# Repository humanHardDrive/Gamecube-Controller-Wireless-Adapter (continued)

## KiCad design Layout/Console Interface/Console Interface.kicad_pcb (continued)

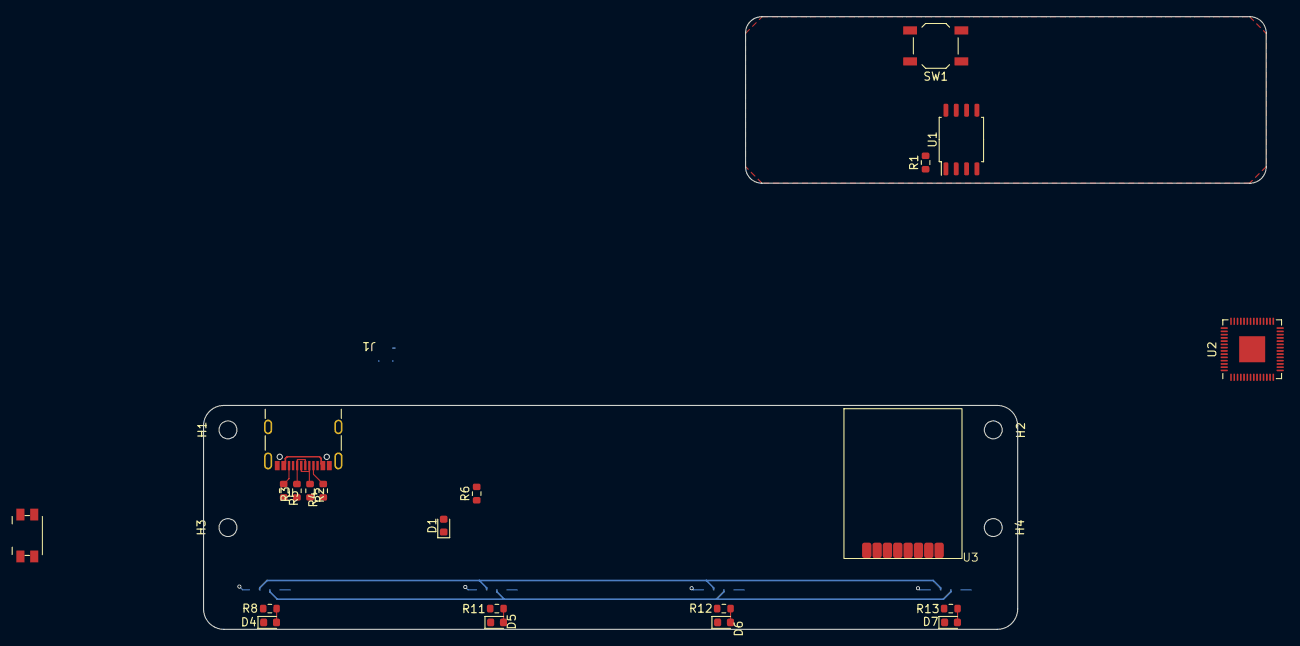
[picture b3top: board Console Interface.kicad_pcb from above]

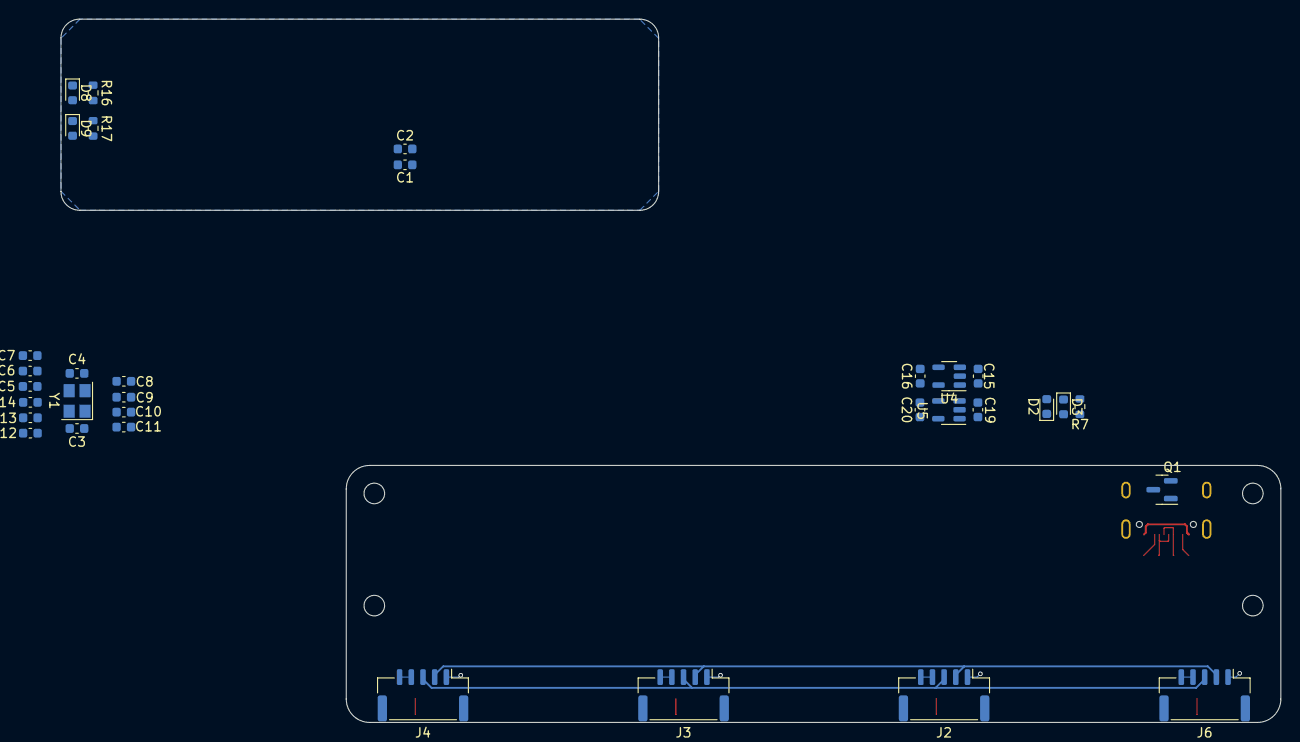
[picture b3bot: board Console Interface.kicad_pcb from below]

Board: 2 copper layers, 130.5 x 75.2 mm, 58 parts (33 on the bottom side), 46 nets.

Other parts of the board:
SW3: SW_PAIR; Panasonic_EVQPUK_EVQPUB

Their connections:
GND: SW3.2; also elsewhere on the board

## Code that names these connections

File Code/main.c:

#include <stdint.h>

#include "pico/stdlib.h"

#include "hardware/gpio.h"
#include "hardware/spi.h"

#include "PinDefs.h"
#include "Utils.h"

#include "ControllerComm.h"

int main()
{
    //Setup pins
    gpio_init(PAIR_PIN);
    gpio_init(FUNC_SEL_PIN);

    gpio_init(NRF_CS_PIN);
    gpio_init(NRF_CE_PIN);
    gpio_init(NRF_IRQ_PIN);

    gpio_set_dir(PAIR_PIN, GPIO_IN);
    gpio_set_dir(FUNC_SEL_PIN, GPIO_IN);

    gpio_pull_up(PAIR_PIN);
    gpio_pull_up(FUNC_SEL_PIN);

    //Setup SPI0
    spi_init(spi_default, 10000000); //NRF supports 10MHz
    gpio_set_function(SPI0_MOSI_PIN, GPIO_FUNC_SPI);
    gpio_set_function(SPI0_MISO_PIN, GPIO_FUNC_SPI);
    gpio_set_function(SPI0_CLK_PIN, GPIO_FUNC_SPI);

    //Detect device configuration
    if(!gpio_get(FUNC_SEL_PIN))
    {
        /*
        This is the controller side interface
        Poll for controller connection
        Poll for controller values
        Report controller values back to the console side interface
        */
       SetInterfaceType(CONTROLLER_SIDE_INTERFACE);
    }
    else
    {
        /*
        This is the console side interface
        Handle polling requests from the console
        Feed console data from controller side interface
        Communicate rumbe back to controller side interface
        */
       SetInterfaceType(CONSOLE_SIDE_INTERFACE);
    }

    ControllerComm_Init();

    while(1)
    {
        ControllerComm_Background();
    }

    return 0;
}

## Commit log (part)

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2024-03-02 Add parts to the controller interface
2024-03-02 Add code
2024-03-03 Add some code
2024-03-03 Fill out pin definitions. Start adding PIO
2024-03-03 Did stuff
2024-03-05 Fix errors
2024-03-05 Testing. Not working.
2024-03-07 Create new project to test controller interface
2024-03-15 Add rx.pio code. Testing
2024-03-15 Better transmit timing. Create loopback test.
    All data looks good. Out matches in for 16 bits
2024-03-15 Add comments
2024-03-15 Copy over working code
2024-03-16 Controller polling is done on a per controller timer
2024-03-17 Fix build
2024-03-17 Begin refactor tx/rx into single PIO
2024-03-17 Nevermind. No refactor
2024-03-17 Enable/disable driver to create open collector functionality. Add more communication interface logic
2024-03-19 Change test to use an open-drain configuration
2024-03-20 Controller adapter testing
2024-03-20 Fix bug setting data length back to a shorter range
2024-03-24 Refactor rx/tx PIO into single program
2024-03-26 Get accurate timing. Successfully test one way communication
2024-03-26 Implement an echo
2024-03-27 Move test code over
2024-03-31 Fix bug causing length to jump an extra bit occasionally
2024-03-31 Add 'stop' state to simplify the send method
2024-03-31 Fix comm bug after controller connected
2024-03-31 Comments
2024-03-31 Signal from PIO to code that read is complete
2024-04-09 Fix tester
2024-04-10 Try and get RX state machine to work with 200kHz
2024-04-12 Make state machine tolerant to more timings
2024-04-12 Change the TX machine to pull length from the OSR
2024-04-13 Fix write length using FIFO
2024-04-15 Functioning transmit with any number of bits
2024-04-18 Successfully read in multiple words
2024-04-19 Full test
2024-04-20 Port changes over from test
2024-04-20 Start implementing NRF control
2024-04-23 NRF updates
2024-04-23 Add NRF24 library
2024-04-23 Rework to a CPP project
2024-04-24 Start implementing high level control
2024-04-24 Add/fill ping-pong buffer
2024-05-04 Semi-functioning wireless
2024-05-15 Remove RF24 submodule
2024-05-15 Add copy of RF24 library so it can be modified
2024-05-16 Optimize the RF library. Still 200uS missing
2024-05-16 Functioning wireless
2024-05-16 Found 200uS
2024-05-17 Successful wireless communication
2024-05-17 Rework controller definitions
2024-05-20 Put back console communication
2024-05-22 Successful console interaction
2024-05-25 Fix bug for short messages
2024-05-26 Console communication is more complicated
2024-06-07 Implement more information about console communication
2024-06-07 Add missing rename
2024-06-08 Functional wireless control!
2024-06-08 Console communication is annoying
2024-06-08 Make wireless more good
2024-06-17 Start working on sleep
2024-06-17 Clean up some pins
2024-06-18 More power control stuff
2024-06-19 More work on the controller layout
2024-07-09 Schematic updates
2024-08-02 Completed schematic and layout
2024-08-05 Via too small
2024-08-05 Add stuff to console interface
2024-08-16 Add plug STL
2024-08-20 Switching regulator footprint doesn't exist
2024-08-20 Create new footprint for plug clamp
2024-09-10 Schematic/PCB fixes
    Fix VUSB supply. Add cut out for antenna wire.
2024-09-25 Changes for hardware
    Implement different pin numbers for different interface types. Add startup routine to controller comm.
2024-09-25 Use UART to debug
2024-11-23 Add console interface schematic
2024-11-23 Fix missing ground
2024-11-25 Fix another missing ground
2024-11-25 Add loopback test
2024-11-25 Code working with actual hardware
2025-04-07 Debugging to improve console interface responsiveness
2025-04-09 Rewrite controller read/write for speed
2025-04-11 Bleeding edge of speed
    The console communication is probably not going to get any faster
2025-04-17 Create a separate board for the LEDs
2025-07-09 Cleanup test code
2025-07-09 Use separate board for lights
